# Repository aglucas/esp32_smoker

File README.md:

# esp32_smoker

ESP32 firmware project for a smoker controller, built on [ESP-IDF v5.5.3](https://github.com/espressif/esp-idf/releases/tag/v5.5.3). Targets the [Seeed Studio XIAO ESP32C3](https://wiki.seeedstudio.com/XIAO_ESP32C3_Getting_Started/).

## Features

- 3 NTC thermistor probes (probe 0 = pit, 1..2 = meat), read in °F. Beta model by default, or per-probe Steinhart-Hart coefficients once calibrated. Unplugged/shorted probes show as `--`.
- Phone-friendly web dashboard at `http://smoker.local` (mDNS) or the device IP: live temps, pit low/high alarm, pit target and per-probe meat targets, and a graph (pit target drawn as a green line, low/high as red lines) of the last 1/2/3/6 hours with touch/hover readout. Fully self-contained (no CDN), so it also works on the offline setup AP.
- Alerts: pit too low (only after it stays low for the "Low alarm delay", 60 s by default and set on the pit card, so opening the lid doesn't trigger it, and only armed once the pit first reaches temp), pit too high, pit probe lost, meat "almost done", meat done. Delivered by [ntfy.sh](https://ntfy.sh) push notifications (set up from the dashboard). Settings are saved in NVS.
- Wi-Fi: tries `DEFAULT_STA_SSID`, then credentials saved in NVS; if neither connects it falls back to a SoftAP (`ESP32-Smoker-XXXX`, password `smoker1234` by default) and the dashboard shows a network picker. Alerts need internet, so none are sent in AP mode (they queue until it reconnects). While in AP mode it retries your Wi-Fi every 60 s (`WIFI_RECONNECT_SEC`) in the background, keeping the AP up meanwhile, and switches back automatically once it connects.
- Graph history: one sample every 30 s for 12 h, kept in RAM. After a power cut, once the clock syncs over the internet (a few seconds after Wi-Fi connects), the graph reloads the last 12 h from the flash log at 1-minute resolution. The outage shows as a break in the lines. On the offline setup AP the clock never syncs, so the graph starts empty (the flash log still has everything).
- Flash log: one CSV row per minute (`uptime_s,unix_time,local_time,<probe>_f...`) saved to a LittleFS partition in the ESP32's internal flash, so no SD card is needed. Download it from the dashboard's **Data log** panel. **Start new recording** (next to it) deletes the log, clears the graph, and re-arms alerts and the meat target-hit checks; settings are kept. `unix_time` and `local_time` (Mountain Time, set by `LOG_TIMEZONE`) are blank until SNTP syncs. When the active file passes 1 MB it is rotated, and the oldest data is dropped, so the log keeps roughly the last 2-4 weeks of cooking.
- Cook steps: named, timed plans (for example "3-2-1 ribs") edited in the **Cook steps** panel. Each step has a name, minutes, an action and a target temp. Plans are saved on the LittleFS partition (`plans.json`); up to 10 plans with up to 12 steps each. **Start** sends step 1's alert right away, then each next step's alert when the previous step's time is up (for example "Step 2/4: The wrap (120 min) - wrapped in foil ribs. Target 120F"), and a final "all steps done" alert. The target temp is only shown in the alert. The running plan is saved too, so after a power cut it resumes once the clock syncs, and a step that began during the outage is sent late with a note.
- Fan control: a 12 V PC fan on GPIO6 (D4) through a 2N2222, driven by slow (50 Hz) PWM, which lets a 2/3-wire PC fan run steadily at lower speeds than fast PWM. **Auto** runs a PID that holds the pit target (starting with Kp = 4 %/°F, Ki = Kd = 0); **Manual** holds a fixed %; **Off**. In Auto the fan is off when no pit target is set or the pit probe has no reading. If the pit reaches the high alarm, the fan turns off and stays off until the pit has cooled back down to the target. The PID output (0-100 %) drives the fan directly; with slow PWM the fan runs steadily down to about 5 %, and any non-zero output below that is raised to 5 % (`FAN_MIN_PCT`). A 1 s full-speed kick runs when the fan starts from stopped. **Fan alert** (Auto mode): if the fan stays at or above a set % for a set time (90 % for 15 min by default, both set in the Fan panel, 0 = off), one alert is sent to say the fire may be low on fuel or the vents may be wrong; it re-arms once the fan drops below that %. The fan % is plotted on its own graph (0-100 %, half the height) under the temperature graph, sharing its time axis, and logged in the CSV (`fan_pct`).
- JSON API: `GET /api/now`, `GET /api/history`, `POST /api/settings` (form-encoded `alertsOn`, `pitLow`, `pitHigh`, `pitTarget`, `pitLowDelay`, `t1`, `t2`), `POST /api/test`, `GET /api/log.csv`, `POST /api/reset`, `POST /api/hit/clear` (`{"probe":1}`, clears a meat target-hit check), `POST /api/fan` (`{"mode":"auto","manual":50,"kp":4,"ki":0,"kd":0,"alertPct":90,"alertMin":15}`), `POST /api/ntfy` (`{"enabled":true,"server":"https://ntfy.sh","topic":"..."}`), `GET/POST /api/plans`, `POST /api/plan/start` (`{"name":"..."}`), `POST /api/plan/stop`, `GET /api/scan`, `POST /api/wifi` (`{"ssid":"...","password":"..."}`).

## Wiring

Each probe is a voltage divider: `3V3 → rRef → pin → thermistor → GND`. Probes must be on ADC1. The XIAO exposes only three ADC1 pins (A0-A2); A3 is on ADC2, which is unreliable on the C3 and blocked by ESP-IDF.

| Signal | XIAO pin | GPIO | Notes |
|---|---|---|---|
| Pit probe | A0 | GPIO2 | ADC1_CH2, rRef 100k (see strapping note) |
| Meat 1 | A1 | GPIO3 | ADC1_CH3, rRef 100k |
| Meat 2 | A2 | GPIO4 | ADC1_CH4, rRef 100k |
| Fan | D4 | GPIO6 | PWM to the 2N2222 base (see fan note) |

- **Probes and resistor values:** all three probes are Maverick ET-72/73 style (about 200 kΩ at room temperature) on 100k divider resistors, using HeaterMeter's Steinhart-Hart coefficients for that probe (`MAVERICK_SH` in [main/config.h](main/config.h)). They were verified against a 180 °F oven and boiling water (about 202 °F at 5,400 ft). The C3's ADC is only accurate up to about 2.5 V (the classic ESP32 reaches about 3.1 V), so below about 49 °F a probe can't be told apart from an unplugged one, and the dashboard shows "below 49° or unplugged".
- **Strapping pin:** GPIO2 (A0) is sampled at reset to choose the boot mode. The pit probe on A0 holds it at 3.3 V when unplugged and about 2.2 V at room temperature. If the board ever fails to boot with the pit probe plugged in, unplug it during power-up.
- **Fan:** GPIO6 → ~220 Ω → 2N2222 base; emitter to GND; collector to the fan's black (−) wire; fan red (+) to 12 V. The 12 V supply's ground must be connected to the XIAO's GND. Add a diode (1N4148 or 1N5819) across the fan, cathode to +12 V, to absorb switching spikes, and a 10 kΩ resistor from base to GND so the fan stays off while the board boots. Around 220 Ω gives the base roughly 10 mA, enough to fully switch a typical 0.1-0.3 A PC fan (1 kΩ may leave the transistor only part-on and hot).
- **Antenna:** the XIAO ESP32C3 needs its external antenna attached for usable Wi-Fi range.

Probe names, pins, resistor values and thermistor constants are in `PROBE_TABLE` in [main/config.h](main/config.h). For accuracy, measure the 3V3 rail and set `VSUPPLY_MV`, and set `OPEN_MV` about 50 mV below what an unplugged probe reads. The serial log prints mV and ohms for every probe every 2 s, which you can use for calibration.

## Alerts setup

- **ntfy:** install the ntfy app. On the dashboard, tap **Change** next to *Notifications* to turn ntfy on or off and set the server and topic. **Random** generates a hard-to-guess topic, and the panel shows a link to subscribe to it. The settings are saved in NVS; `NTFY_SERVER`, `NTFY_TOPIC` and `USE_NTFY` in [main/config.h](main/config.h) are only first-boot defaults.

Use **Send test alert** on the dashboard to check delivery.

- **Offline delivery:** alerts raised while Wi-Fi or the internet is down are queued and sent once it's back, marked "(sent N min late)". Failed sends are retried every 30 s. Alerts undelivered after 2 hours are dropped, and a power cut loses the queue.
- **Pit low after a reboot:** the pit low alarm stays armed after a reboot if the board was running within the last 2 hours (`PIT_ARM_RESTORE_MIN`), so a power blip mid-cook doesn't disarm it. A cold start the next day begins disarmed, as usual.

## Prerequisites

- ESP-IDF v5.5.3 installed and set up (`install.bat` / `export.bat` from the IDF repo, or the ESP-IDF VS Code extension).

## Build

```
idf.py set-target esp32c3
idf.py build
```

To have the smoker join your Wi-Fi without using the setup page, copy `main/secrets.h.example` to `main/secrets.h` and fill in your network name and password. `secrets.h` is git-ignored, so the password never gets committed. Without it, the firmware still builds and you pick a network from the dashboard instead.

## Flash & Monitor

```
idf.py -p <PORT> flash monitor
```

`flash` writes the bootloader, the partition table ([partitions.csv](partitions.csv)) and the app together. NVS, which holds Wi-Fi credentials and alert settings, keeps the same place in flash, so those survive a firmware update. The log partition is formatted automatically on first boot.

The XIAO's USB-C port is the C3's built-in USB serial port, and the log console is set to use it. If flashing can't connect, hold **BOOT**, tap **RESET**, then release **BOOT** to enter download mode.

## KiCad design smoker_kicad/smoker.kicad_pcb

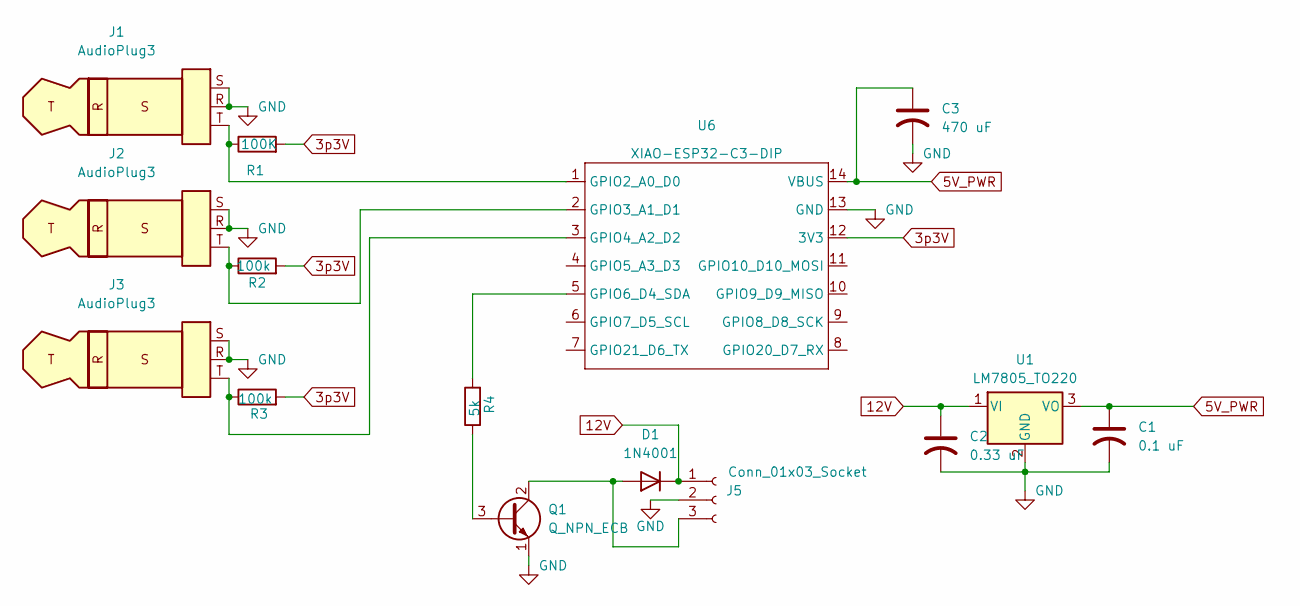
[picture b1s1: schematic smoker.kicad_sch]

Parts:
C1: 0.1 uF; C_0805_2012Metric
C2: 0.33 uF; C_0805_2012Metric
C3: 470 uF; C_Radial_D10.0mm_H16.0mm_P5.00mm
D1: 1N4001; D_DO-41_SOD81_P10.16mm_Horizontal
J1, J2, J3: AudioPlug3; PJ-208_XKB_2.5mm_ThroughHole2
J5: Conn_01x03_Socket; JST_XH_B3B-XH-A_1x03_P2.50mm_Vertical
Q1: Q_NPN_ECB; TO-92
R1: 100K; R_0805_2012Metric_Pad1.20x1.40mm_HandSolder
R2, R3: 100k; R_0805_2012Metric_Pad1.20x1.40mm_HandSolder
R4: 5k; R_0805_2012Metric_Pad1.20x1.40mm_HandSolder
U1: LM7805_TO220; TO-220-3_Vertical
U6: XIAO-ESP32-C3-DIP; MCU_Seeed_ESP32C3

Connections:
3p3V: R1.2, R2.2, R3.2, U6.12 (3V3)
5V_PWR: C1.1, C3.1, U1.3 (VO), U6.14 (VBUS)
12V: C2.1, D1.1 (K), J5.1, U1.1 (VI)
GND: C1.2, C2.2, C3.2, J1.R, J1.S, J2.R, J2.S, J3.R, J3.S, J5.2, Q1.1 (E), U1.2 (GND), U6.13 (GND)
unnamed: D1.2 (A), J5.3, Q1.2 (C)
unnamed: Q1.3 (B), R4.1
unnamed: J1.T, R1.1, U6.1 (GPIO2_A0_D0)
unnamed: J2.T, R2.1, U6.2 (GPIO3_A1_D1)
unnamed: J3.T, R3.1, U6.3 (GPIO4_A2_D2)
unnamed: R4.2, U6.5 (GPIO6_D4_SDA)

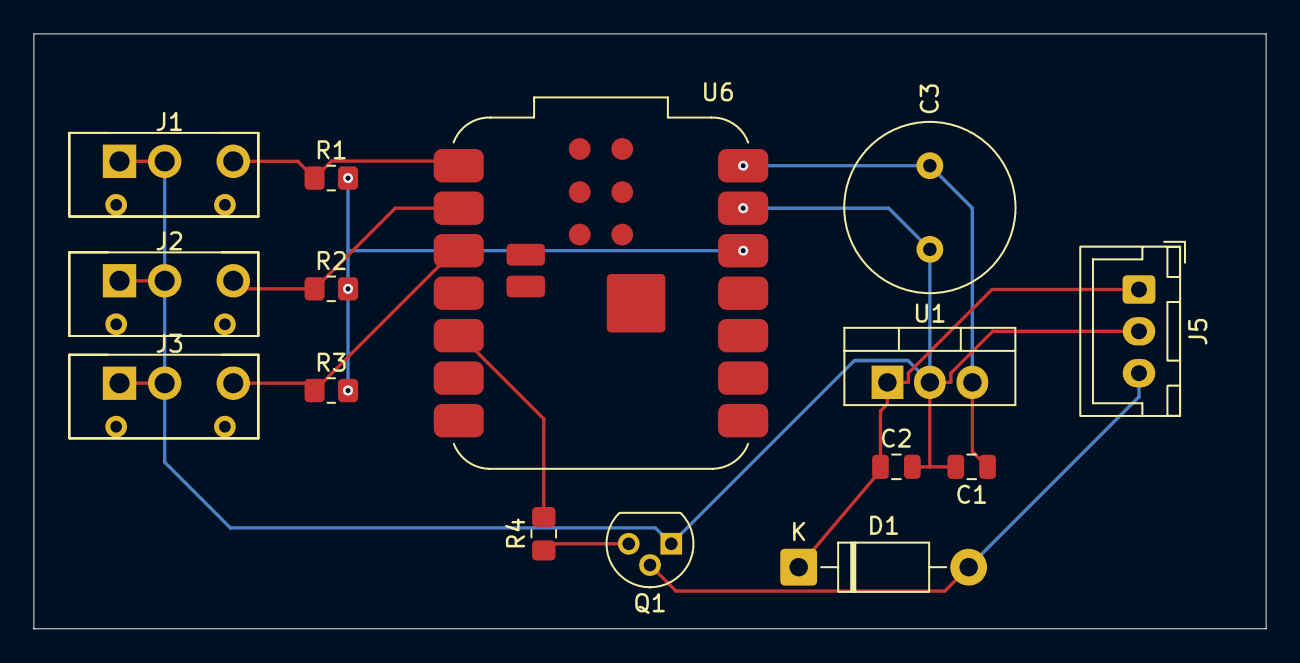
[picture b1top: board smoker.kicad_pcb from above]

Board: 2 copper layers, 73.7 x 35.6 mm, 15 parts (0 on the bottom side), 10 nets.
